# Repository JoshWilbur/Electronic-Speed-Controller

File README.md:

# Electronic-Speed-Controller

Developers: Amir Seidakhmetov and Joshua Wilbur

This repository contains firmware to drive a 36V Electronic Speed Controller (ESC) for a DC motor. This project has been tested to handle a 3A load without issue. Motor speed is monitored and controlled using a hall effect sensor and PID feedback.

Driver code for the H-Bridge circuit is found in /Core/Src. The files main.c,
H_bridge.c, user_input.c and rpm_feedback.c contain custom code developed
for this project.

Images of the project are found below, along with an operation guide.

**Load Testing**

# Operation Guide

* Construct circuit shown in the latest schematic version with the parts listed in the expense report.
* Optional: Order two PCBs using the files in /H_Bridge_KiCAD and /STM32_KiCAD.
* Program STM32 chip with the code, found in this repository, using SWD.
* Power on circuit and controller.
* For safety, the device starts in an OFF state. Shift the direction switch once to begin operation.
* Use the potentiometer to set a desired speed within the range of 60 to 200 RPM.

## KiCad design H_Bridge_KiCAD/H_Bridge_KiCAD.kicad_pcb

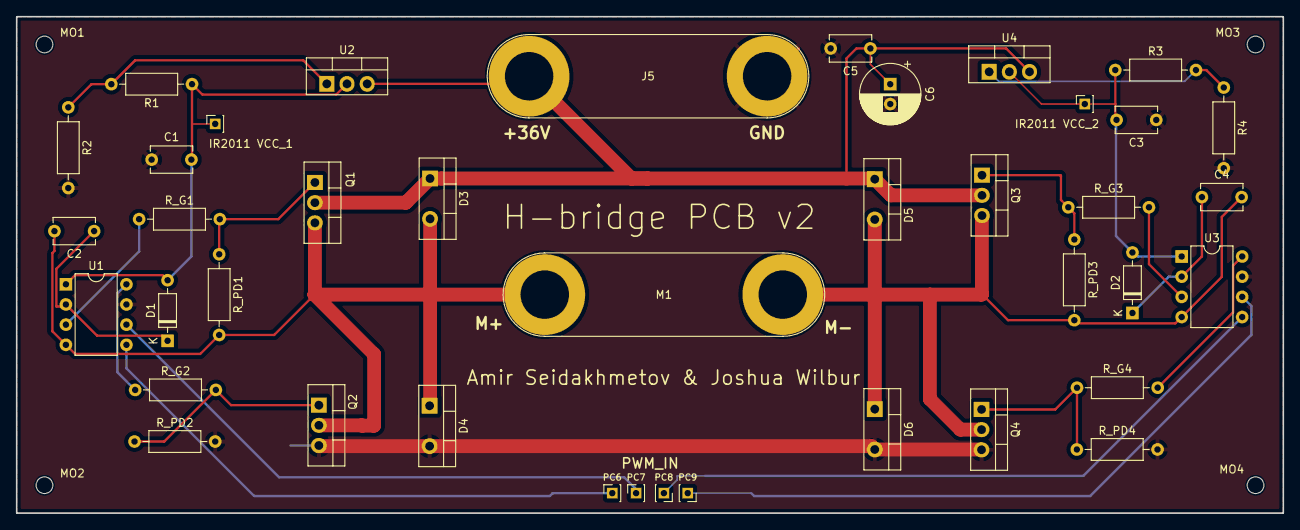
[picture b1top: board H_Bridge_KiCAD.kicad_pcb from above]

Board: 2 copper layers, 159.5 x 62.5 mm, 44 parts (0 on the bottom side), 22 nets.

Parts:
C1, C2, C3, C4, C5: 0.1u; C_Disc_D5.1mm_W3.2mm_P5.00mm
C6: 100u; CP_Radial_D7.5mm_P2.50mm
D1, D2: 1N4148; D_DO-35_SOD27_P7.62mm_Horizontal
D3, D4, D5, D6: MBRF10200; TO-220-2_Vertical
IR2011 VCC_1, IR2011 VCC_2: PinSocket_1x01_P2.00mm_Vertical
J5: Screw_Terminal_01x02; Banana_Jack_2Pin
M1: MY6812; Banana_Jack_2Pin
MO1, MO2, MO3, MO4: MountingHole; MountingHole_2.1mm
PC6, PC7, PC8, PC9: 1x1 Pin Header; PinSocket_1x01_P2.00mm_Vertical
Q1, Q2, Q3, Q4: IRF530N; TO-220-3_Vertical
R1, R3: 470; R_Axial_DIN0207_L6.3mm_D2.5mm_P10.16mm_Horizontal
R2, R4: 5.6k; R_Axial_DIN0207_L6.3mm_D2.5mm_P10.16mm_Horizontal
R_G1, R_G2, R_G3, R_G4: 100; R_Axial_DIN0207_L6.3mm_D2.5mm_P10.16mm_Horizontal
R_PD1, R_PD2, R_PD3, R_PD4: 5.6k; R_Axial_DIN0207_L6.3mm_D2.5mm_P10.16mm_Horizontal
U1, U3: IR2011; DIP-8_W7.62mm
U2, U4: LM317_TO-220; TO-220-3_Vertical

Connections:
+36V: C5.1, C6.1, D3.1 (K), D5.1 (K), J5.2, Q1.2 (D), Q3.2 (D), U2.3 (VI), U4.3 (VI)
GND: C1.1, C3.1, C5.2, C6.2, D4.2 (A), D6.2 (A), J5.1, Q2.3 (S), Q4.3 (S), R2.2, R4.2, R_PD2.2, R_PD4.2, U1.7 (COM), U3.7 (COM)
unnamed: C1.2, D1.2 (A), IR2011 VCC_1.1, R1.1, U1.1 (VCC), U2.2 (VO)
unnamed: C2.1, D1.1 (K), U1.2 (VB)
unnamed: C3.2, D2.2 (A), IR2011 VCC_2.1, R3.1, U3.1 (VCC), U4.2 (VO)
unnamed: C4.1, D2.1 (K), U3.2 (VB)
unnamed: C2.2, D3.2 (A), D4.1 (K), M1.1 (+), Q1.3 (S), Q2.2 (D), R_PD1.2, U1.4 (VS)
unnamed: C4.2, D5.2 (A), D6.1 (K), M1.2 (-), Q3.3 (S), Q4.2 (D), R_PD3.2, U3.4 (VS)
unnamed: Q1.1 (G), R_G1.2, R_PD1.1
unnamed: Q2.1 (G), R_G2.2, R_PD2.1
unnamed: Q3.1 (G), R_G3.1, R_PD3.1
unnamed: Q4.1 (G), R_G4.1, R_PD4.1
unnamed: R_G1.1, U1.3 (HO)
unnamed: R_G2.1, U1.8 (LO)
unnamed: R1.2, R2.1, U2.1 (ADJ)
unnamed: R_G3.2, U3.3 (HO)
unnamed: R_G4.2, U3.8 (LO)
unnamed: R3.2, R4.1, U4.1 (ADJ)
PWM_IN1: PC6.1, U1.5 (HIN)
PWM_IN2: PC7.1, U1.6 (LIN)
PWM_IN3: PC8.1, U3.5 (HIN)
PWM_IN4: PC9.1, U3.6 (LIN)

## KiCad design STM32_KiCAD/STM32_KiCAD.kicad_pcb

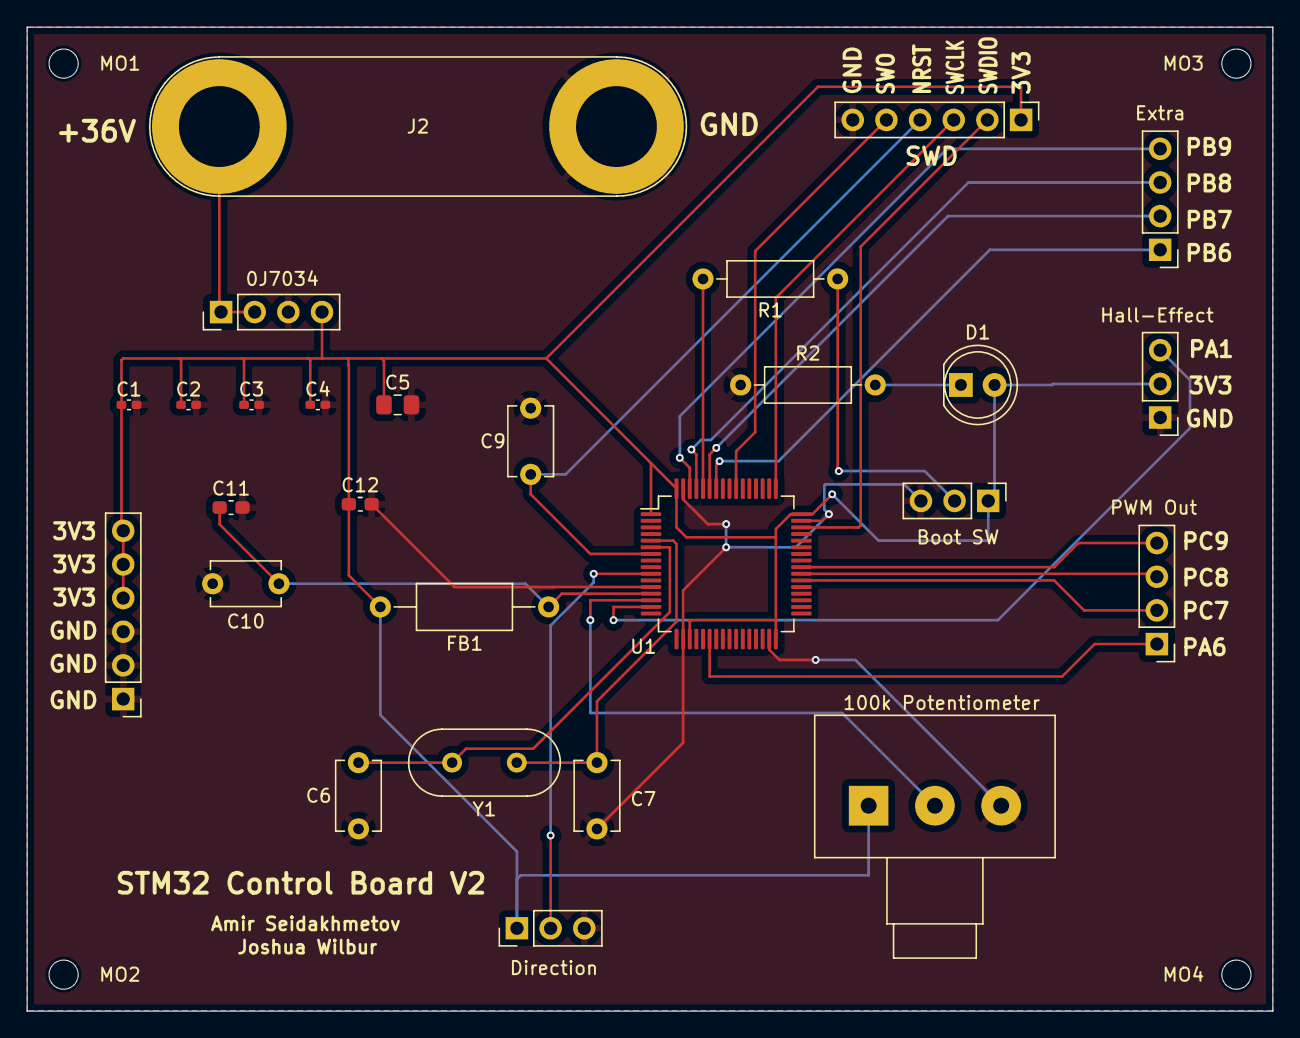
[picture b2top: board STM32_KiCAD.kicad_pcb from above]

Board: 2 copper layers, 94.0 x 74.2 mm, 31 parts (0 on the bottom side), 24 nets.

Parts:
0J7034: 0J7034; PinHeader_1x04_P2.54mm_Vertical
100k Potentiometer: 100k; Potentiometer_Alps_RK163_Single_Horizontal
Boot SW: Boot SW; PinHeader_1x03_P2.54mm_Vertical
C1, C2, C3, C4: 0.1u; C_0402_1005Metric_Pad0.74x0.62mm_HandSolder
C5: 4.7u; C_0805_2012Metric_Pad1.18x1.45mm_HandSolder
C6, C7: 20pF; C_Disc_D5.1mm_W3.2mm_P5.00mm
C9: 0.1u; C_Disc_D5.1mm_W3.2mm_P5.00mm
C10: 0.01u; C_Disc_D5.1mm_W3.2mm_P5.00mm
C11, C12: 1u; C_0603_1608Metric_Pad1.08x0.95mm_HandSolder
D1: LED; LED_D5.0mm
Direction: Dir SW; PinHeader_1x03_P2.54mm_Vertical
Extra: Extra; PinHeader_1x04_P2.54mm_Vertical
FB1: 976 Ohm @ 100MHz; L_Axial_L7.0mm_D3.3mm_P12.70mm_Horizontal_Fastron_MICC
Hall-Effect: Hall-Effect Sensor; PinHeader_1x03_P2.54mm_Vertical
J2: Screw_Terminal_01x02; Banana_Jack_2Pin
J6: Power Pins; PinHeader_1x06_P2.54mm_Vertical
MO1, MO2, MO3, MO4: MountingHole_2.2mm_M2
PWM Out: PWM Out; PinHeader_1x04_P2.54mm_Vertical
R1: 10k; R_Axial_DIN0207_L6.3mm_D2.5mm_P10.16mm_Horizontal
R2: 2.2k; R_Axial_DIN0207_L6.3mm_D2.5mm_P10.16mm_Horizontal
SWD: SWD; PinHeader_1x06_P2.54mm_Vertical
U1: STM32L476RG; LQFP-64_10x10mm_P0.5mm
Y1: 8MHz; Crystal_HC49-4H_Vertical

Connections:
+3V3: 0J7034.4, 100k Potentiometer.1, Boot SW.1 (C), C1.1, C2.1, C3.1, C4.1, C5.1, C12.1, D1.2 (A), Direction.1 (C), FB1.2, Hall-Effect.2, J6.4, J6.5, J6.6, SWD.1, U1.1 (VBAT), U1.19 (VDD), U1.32 (VDD), U1.48 (VDDUSB), U1.64 (VDD)
/NRST: C9.1, SWD.4, U1.7 (NRST)
/PWM_1: PWM Out.1, U1.22 (PA6)
/SWCLK: SWD.3, U1.49 (PA14)
/SWDIO: SWD.2, U1.46 (PA13)
/SWO: SWD.5, U1.55 (PB3)
/VIN: 0J7034.1, 0J7034.2, J2.1
GND: 0J7034.3, 100k Potentiometer.3, Boot SW.3 (A), C1.2, C2.2, C3.2, C4.2, C5.2, C6.2, C7.2, C9.2, C10.2, C11.2, C12.2, Direction.3 (A), Hall-Effect.1, J2.2, J6.1, J6.2, J6.3, R2.1, SWD.6, U1.12 (VSSA), U1.18 (VSS), U1.31 (VSS), U1.47 (VSS), U1.63 (VSS)
unnamed: D1.1 (K), R2.2
unnamed: PWM Out.2, U1.38 (PC7)
unnamed: PWM Out.3, U1.39 (PC8)
unnamed: PWM Out.4, U1.40 (PC9)
unnamed: Extra.1, U1.58 (PB6)
unnamed: Extra.2, U1.59 (PB7)
unnamed: Extra.3, U1.61 (PB8)
unnamed: Extra.4, U1.62 (PB9)
unnamed: Boot SW.2 (B), R1.1
unnamed: R1.2, U1.60 (BOOT0)
unnamed: C7.1, U1.5 (PH0), Y1.1
unnamed: C6.1, U1.6 (PH1), Y1.2
unnamed: C10.1, C11.1, FB1.1, U1.13 (VDDA)
PA0_ADC: 100k Potentiometer.2, U1.14 (PA0)
PA1_ADC: Hall-Effect.3, U1.15 (PA1)
PC2_EXTI2: Direction.2 (B), U1.10 (PC2)

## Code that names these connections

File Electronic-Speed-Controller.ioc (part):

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Mcu.Name=STM32L476R(C-E-G)Tx
Mcu.Package=LQFP64
Mcu.UserName=STM32L476RGTx
PA0.Signal=ADCx_IN5
PA1.Signal=ADCx_IN6
PA13\ (JTMS-SWDIO).Mode=Trace_Asynchronous_SW
PA13\ (JTMS-SWDIO).Signal=SYS_JTMS-SWDIO
PA14\ (JTCK-SWCLK).Mode=Trace_Asynchronous_SW
PA14\ (JTCK-SWCLK).Signal=SYS_JTCK-SWCLK
PA6.Signal=S_TIM3_CH1
PB3\ (JTDO-TRACESWO).Mode=Trace_Asynchronous_SW
PB3\ (JTDO-TRACESWO).Signal=SYS_JTDO-SWO
PB6.Mode=I2C
PB6.Signal=I2C1_SCL
PB7.Mode=I2C
PB7.Signal=I2C1_SDA
PC1.GPIOParameters=GPIO_ModeDefaultEXTI
PC1.GPIO_ModeDefaultEXTI=GPIO_MODE_IT_FALLING
PC1.Signal=GPXTI1
PC2.GPIOParameters=GPIO_ModeDefaultEXTI
PC2.GPIO_ModeDefaultEXTI=GPIO_MODE_IT_RISING_FALLING
PC2.Signal=GPXTI2
PC7.Signal=S_TIM3_CH2
PC8.Signal=S_TIM3_CH3
PC9.Signal=S_TIM3_CH4
PH0-OSC_IN\ (PH0).Mode=HSE-External-Oscillator
PH0-OSC_IN\ (PH0).Signal=RCC_OSC_IN
PH1-OSC_OUT\ (PH1).Mode=HSE-External-Oscillator
PH1-OSC_OUT\ (PH1).Signal=RCC_OSC_OUT
RCC.HSE_VALUE=8000000
RCC.SYSCLKFreq_VALUE=72000000
RCC.SYSCLKSource=RCC_SYSCLKSOURCE_PLLCLK
board=custom

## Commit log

2024-05-03 test commit from CubeIDE
2024-05-03 added gitignore
2024-05-03 basic LED blinking program
2024-05-04 added basic H bridge control programs
2024-05-04 test commit after resetting IDE
2024-07-11 Moved HAL code out of main.c into its own file
2024-07-11 Updated .ioc file to add PWM capability
2024-07-15 Test commit from Linux
2024-07-15 test commit from arch linux
2024-07-16 H-Bridge state program added, allows clockwise/coclockwise motor rotation
2024-07-16 Added comments to H-Bridge state program
2024-07-19 Created and debugged the potentiometer input program
2024-07-19 test commit to fix issue
2024-07-19 Found and moved H_Bridge.c to /Core/Src
2024-07-23 Fine tuned PWM frequency to 25kHz
2024-07-24 Update README.md with image
2024-07-28 Optimize state program
2024-08-03 Added image of H Bridge prototype (v1)
2024-08-20 Added H-bridge circuit schematic (V2)
2024-08-21 Revise design slightly
2024-09-04 flesh out code comments and add TODO to README
2024-09-08 add updated schematic with bypass caps
2024-09-12 Clean up unused pins and formatting
2024-09-12 setup for EXTI1 interrupt complete
2024-09-13 create interrupts for pulse counting and RPM processing
2024-09-16 created function for adjusting PWM frequency, needs testing
2024-09-17 complete PWM frequency function
2024-09-20 debugged pulse counting interrupts
2024-09-20 setup PC2, add guards to header files
2024-09-20 add dead time and interrupt for switching motor direction
2024-09-21 Upload ESC schematic v1.0
2024-09-21 reset unused GPIO pins
2024-09-23 set up ADC for DMA
2024-09-23 more work done on ADC, TODO fix ADC1_CH1 output
2024-09-24 some debugging on the ADC channel, changed pins
2024-09-25 more debugging, no solution yet...
2024-09-25 Test commit from laptop
2024-09-25 switch ADC inputs to use polling
2024-09-25 remove DMA code, clean up comments
2024-09-30 change bypass caps to 0.1uF
2024-10-08 new schematic revision
    revised high side mosfet pull downs to attach to source instead of ground. modified flyback diodes, other ones are too small
2024-10-08 small update to schematic v4
    added power and pin connectors
2024-10-09 clean up files, build framework for feedback code
2024-10-15 hall effect RPM function working
2024-10-17 develop proportional control function
2024-10-23 upload version 5 of ESC schematic
    mostly resistor value changes, updated diode on gate driver to reflect prototype
2024-10-25 fine tune hall effect RPM code
2024-10-28 create SWD pins for programming
2024-10-28 Add rate limiting to input
2024-10-30 limit speed to prevent inductive kickback
2024-11-01 upload STM32 control board schematic
2024-11-05 updates to feedback after testing, more work needed...
2024-11-08 implemented feedback code, reworked user input as well
2024-11-13 improve and bound user input code
2024-11-13 Battery sensing
    adding initial battery sensing
2024-11-13 finished fixing user input, switch PC6 to PA6
2024-11-15 upload H-Bridge schematic v6
2024-11-15 closed loop feedback implemented
2024-11-16 set PB3 as SWO pin
2024-11-16 upload STM32 schematic V2
2024-11-17 update TODO
2024-11-18 update code to account for geared down motor
2024-11-19 revise schematic v6 to add battery protection
2024-11-20 limit input range from 60-200 RPM, further tune feedback
2024-11-22 increase minimum RPM to 60 in lerp function
2024-11-25 Adding first version of PID feedback control
    Preliminary execution of PID feedback control
2024-12-04 MIN_INPUT adjustment + PID
    Adjusting MIN_INPUT variable to match 60rpm due to changed resistors - verified imperially by adjusting the value and measuring minimum rpm of the motor until it reaches ~60
    Changing PID constants to global variables for troubleshooting
2024-12-05 Finish PID variable tuning, re-add code that got lost
2024-12-05 Code to make 7-segment display work
2024-12-05 updating to display real_rpm
2024-12-05 move 7 segment code into it's own file, make header file
2024-12-05 tune PID for 36V
2024-12-06 changed RPM sampling time to 0.25s, further tuned PID
2024-12-08 Upload PCB files, clean up code and add comments
2024-12-11 update schematics to match current circuit
2024-12-13 upload expense report and references
2024-12-14 increased Kp and modified hall effect bounds
2024-12-15 upload revised STM32 schematic
    Buck converter IC failed on Friday, this schematic has a new voltage step down method
2024-12-15 fix errors on schematic
2025-03-09 updated schematics to reflect current circuit + corrections
2025-03-10 code changes for prior state
2025-03-11 update H-bridge schematic after feedback
2025-03-12 uploaded report and tex files
2025-03-14 add images to README
2025-04-20 upload capstone presentation
